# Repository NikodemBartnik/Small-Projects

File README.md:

# Small Projects
Here you can find some of my smaller projects. Most of them are Arduino based, there are also schematics and PCB design files. Feel free to fork and make it even better! Don't forget to share with others and with me, I would love to see how you adapt those small projects into something bigger :)

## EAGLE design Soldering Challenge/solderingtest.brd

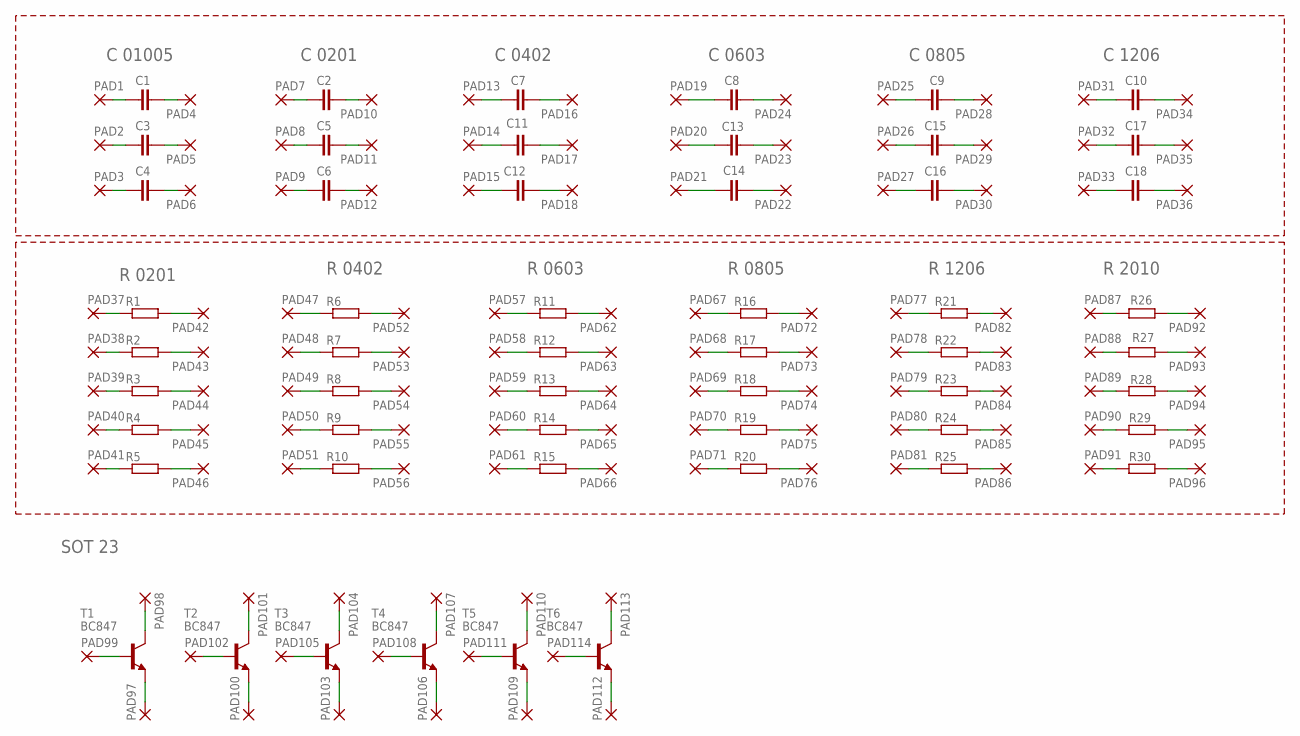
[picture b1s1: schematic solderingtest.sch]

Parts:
C1, C3, C4: C-EU01005; C01005
C2, C5, C6: C-EUC0201; C0201
C7, C11, C12: C-EUC0402; C0402
C8, C13, C14: C-EUC0603; C0603
C9, C15, C16: C-EUC0805; C0805
C10, C17, C18: C-EUC1206; C1206
PAD1, PAD2, PAD3, PAD4, PAD5, PAD6, PAD7, PAD8, PAD9, PAD10, PAD11, PAD12, PAD13, PAD14, PAD15, PAD16, PAD17, PAD18, PAD19, PAD20, PAD21, PAD22, PAD23, PAD24, PAD25, PAD26, PAD27, PAD28, PAD29, PAD30, PAD31, PAD32, PAD33, PAD34, PAD35, PAD36, PAD37, PAD38, PAD39, PAD40, PAD41, PAD42, PAD43, PAD44, PAD45, PAD46, PAD47, PAD48, PAD49, PAD50, PAD51, PAD52, PAD53, PAD54, PAD55, PAD56, PAD57, PAD58, PAD59, PAD60, PAD61, PAD62, PAD63, PAD64, PAD65, PAD66, PAD67, PAD68, PAD69, PAD70, PAD71, PAD72, PAD73, PAD74, PAD75, PAD76, PAD77, PAD78, PAD79, PAD80, PAD81, PAD82, PAD83, PAD84, PAD85, PAD86, PAD87, PAD88, PAD89, PAD90, PAD91, PAD92, PAD93, PAD94, PAD95, PAD96, PAD97, PAD98, PAD99, PAD100, PAD101, PAD102, PAD103, PAD104, PAD105, PAD106, PAD107, PAD108, PAD109, PAD110, PAD111, PAD112, PAD113, PAD114: 2,54/1,0
R1, R2, R3, R4, R5: R-EU_R0201; R0201
R6, R7, R8, R9, R10: R-EU_R0402; R0402
R11, R12, R13, R14, R15: R-EU_R0603; R0603
R16, R17, R18, R19, R20: R-EU_R0805; R0805
R21, R22, R23, R24, R25: R-EU_R1206; R1206
R26, R27, R28, R29, R30: R-EU_R2010; R2010
T1, T2, T3, T4, T5, T6: BC847; SOT23

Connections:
unnamed: C1.1, PAD1.1
unnamed: C3.1, PAD2.1
unnamed: C4.1, PAD3.1
unnamed: C4.2, PAD6.1
unnamed: C3.2, PAD5.1
unnamed: C1.2, PAD4.1
unnamed: C2.1, PAD7.1
unnamed: C2.2, PAD10.1
unnamed: C5.2, PAD11.1
unnamed: C5.1, PAD8.1
unnamed: C6.1, PAD9.1
unnamed: C6.2, PAD12.1
unnamed: C7.1, PAD13.1
unnamed: C7.2, PAD16.1
unnamed: C11.2, PAD17.1
unnamed: C11.1, PAD14.1
unnamed: C12.1, PAD15.1
unnamed: C12.2, PAD18.1
unnamed: C8.1, PAD19.1
unnamed: C8.2, PAD24.1
unnamed: C13.2, PAD23.1
unnamed: C14.2, PAD22.1
unnamed: C14.1, PAD21.1
unnamed: C13.1, PAD20.1
unnamed: C9.1, PAD25.1
unnamed: C15.1, PAD26.1
unnamed: C16.1, PAD27.1
unnamed: C9.2, PAD28.1
unnamed: C15.2, PAD29.1
unnamed: C16.2, PAD30.1
unnamed: C10.1, PAD31.1
unnamed: C17.1, PAD32.1
unnamed: C18.1, PAD33.1
unnamed: C10.2, PAD34.1
unnamed: C17.2, PAD35.1
unnamed: C18.2, PAD36.1
unnamed: PAD37.1, R1.1
unnamed: PAD42.1, R1.2
unnamed: PAD43.1, R2.2
unnamed: PAD44.1, R3.2
unnamed: PAD45.1, R4.2
unnamed: PAD40.1, R4.1
unnamed: PAD39.1, R3.1
unnamed: PAD38.1, R2.1
unnamed: PAD41.1, R5.1
unnamed: PAD46.1, R5.2
unnamed: PAD47.1, R6.1
unnamed: PAD52.1, R6.2
unnamed: PAD53.1, R7.2
unnamed: PAD54.1, R8.2
unnamed: PAD55.1, R9.2
unnamed: PAD56.1, R10.2
unnamed: PAD51.1, R10.1
unnamed: PAD50.1, R9.1
unnamed: PAD49.1, R8.1
unnamed: PAD48.1, R7.1
unnamed: PAD58.1, R12.1
unnamed: PAD59.1, R13.1
unnamed: PAD60.1, R14.1
unnamed: PAD61.1, R15.1
unnamed: PAD66.1, R15.2
unnamed: PAD65.1, R14.2
unnamed: PAD64.1, R13.2
unnamed: PAD63.1, R12.2
unnamed: PAD57.1, R11.1
unnamed: PAD62.1, R11.2
unnamed: PAD67.1, R16.1
unnamed: PAD68.1, R17.1
unnamed: PAD69.1, R18.1
unnamed: PAD70.1, R19.1
unnamed: PAD71.1, R20.1
unnamed: PAD76.1, R20.2
unnamed: PAD75.1, R19.2
unnamed: PAD74.1, R18.2
unnamed: PAD73.1, R17.2
unnamed: PAD72.1, R16.2
unnamed: PAD77.1, R21.1
unnamed: PAD78.1, R22.1
unnamed: PAD79.1, R23.1
unnamed: PAD80.1, R24.1
unnamed: PAD81.1, R25.1
unnamed: PAD82.1, R21.2
unnamed: PAD83.1, R22.2
unnamed: PAD84.1, R23.2
unnamed: PAD85.1, R24.2
unnamed: PAD86.1, R25.2
unnamed: PAD87.1, R26.1
unnamed: PAD88.1, R27.1
unnamed: PAD89.1, R28.1
unnamed: PAD90.1, R29.1
unnamed: PAD91.1, R30.1
unnamed: PAD92.1, R26.2
unnamed: PAD93.1, R27.2
unnamed: PAD94.1, R28.2
unnamed: PAD95.1, R29.2
unnamed: PAD96.1, R30.2
unnamed: PAD99.1, T1.1 (B)
unnamed: PAD98.1, T1.3 (C)
unnamed: PAD97.1, T1.2 (E)
unnamed: PAD102.1, T2.1 (B)
unnamed: PAD101.1, T2.3 (C)
unnamed: PAD100.1, T2.2 (E)
unnamed: PAD105.1, T3.1 (B)
unnamed: PAD104.1, T3.3 (C)
unnamed: PAD103.1, T3.2 (E)
unnamed: PAD108.1, T4.1 (B)
unnamed: PAD107.1, T4.3 (C)
unnamed: PAD106.1, T4.2 (E)
unnamed: PAD111.1, T5.1 (B)
unnamed: PAD110.1, T5.3 (C)
unnamed: PAD109.1, T5.2 (E)
unnamed: PAD114.1, T6.1 (B)
unnamed: PAD113.1, T6.3 (C)
unnamed: PAD112.1, T6.2 (E)

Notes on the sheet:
C 01005
C 0201
C 0402
C 0603
C 0805
C 1206
R 0201
R 0402
R 0603
R 0805
R 1206
R 2010
SOT 23

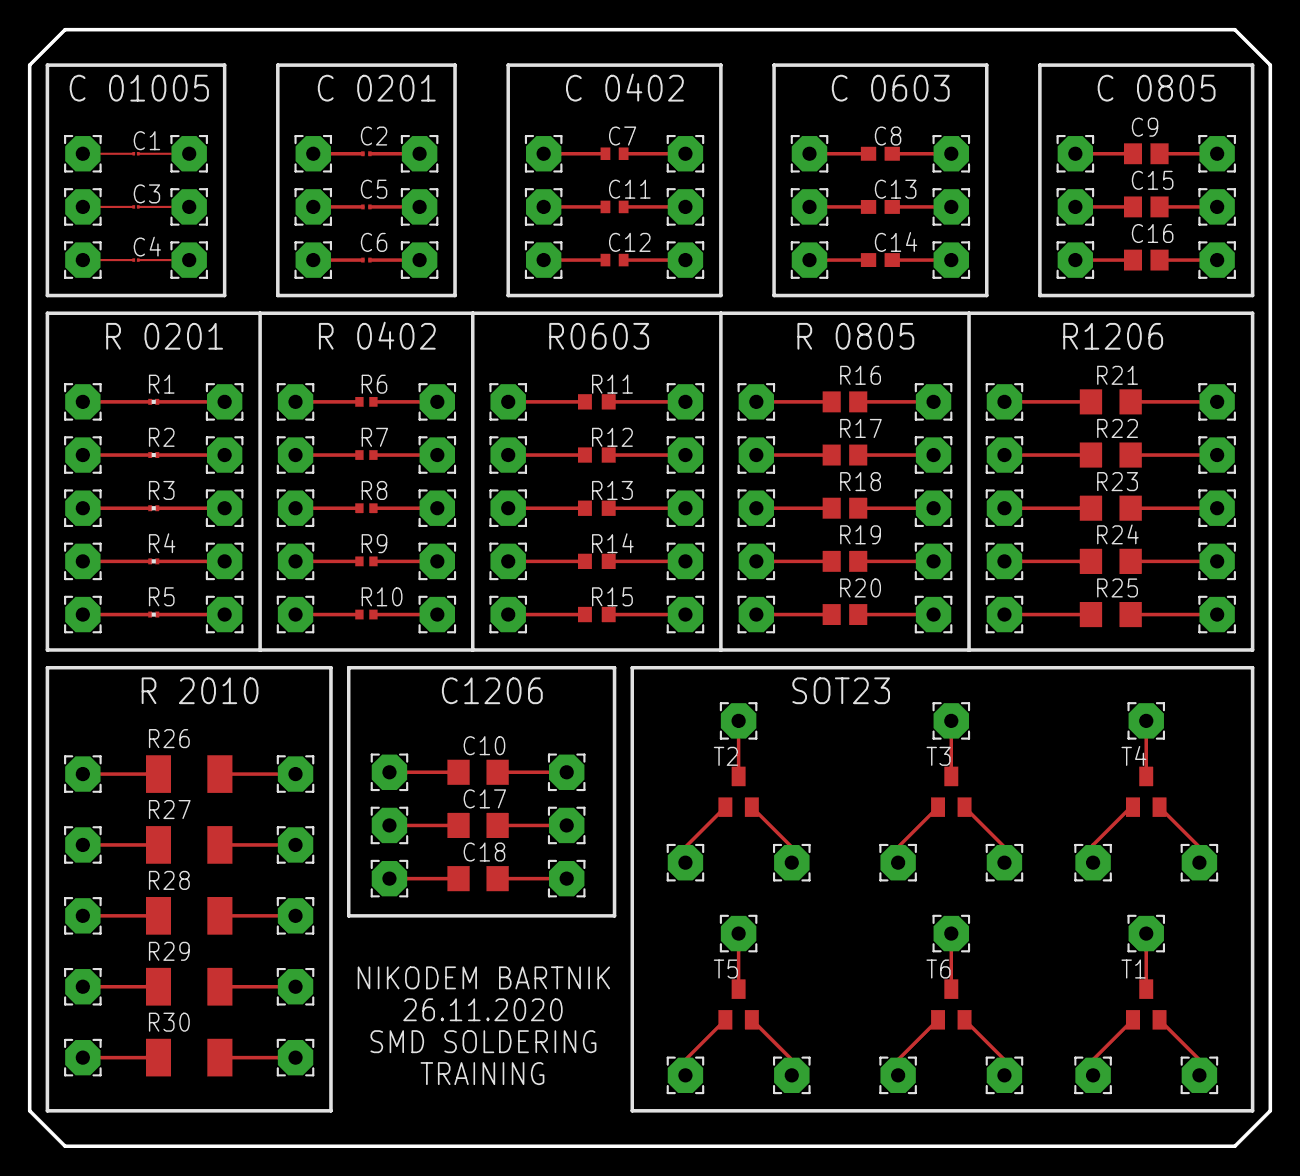
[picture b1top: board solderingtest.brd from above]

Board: 2 copper layers, 88.9 x 80.0 mm, 168 parts (0 on the bottom side), 114 nets.

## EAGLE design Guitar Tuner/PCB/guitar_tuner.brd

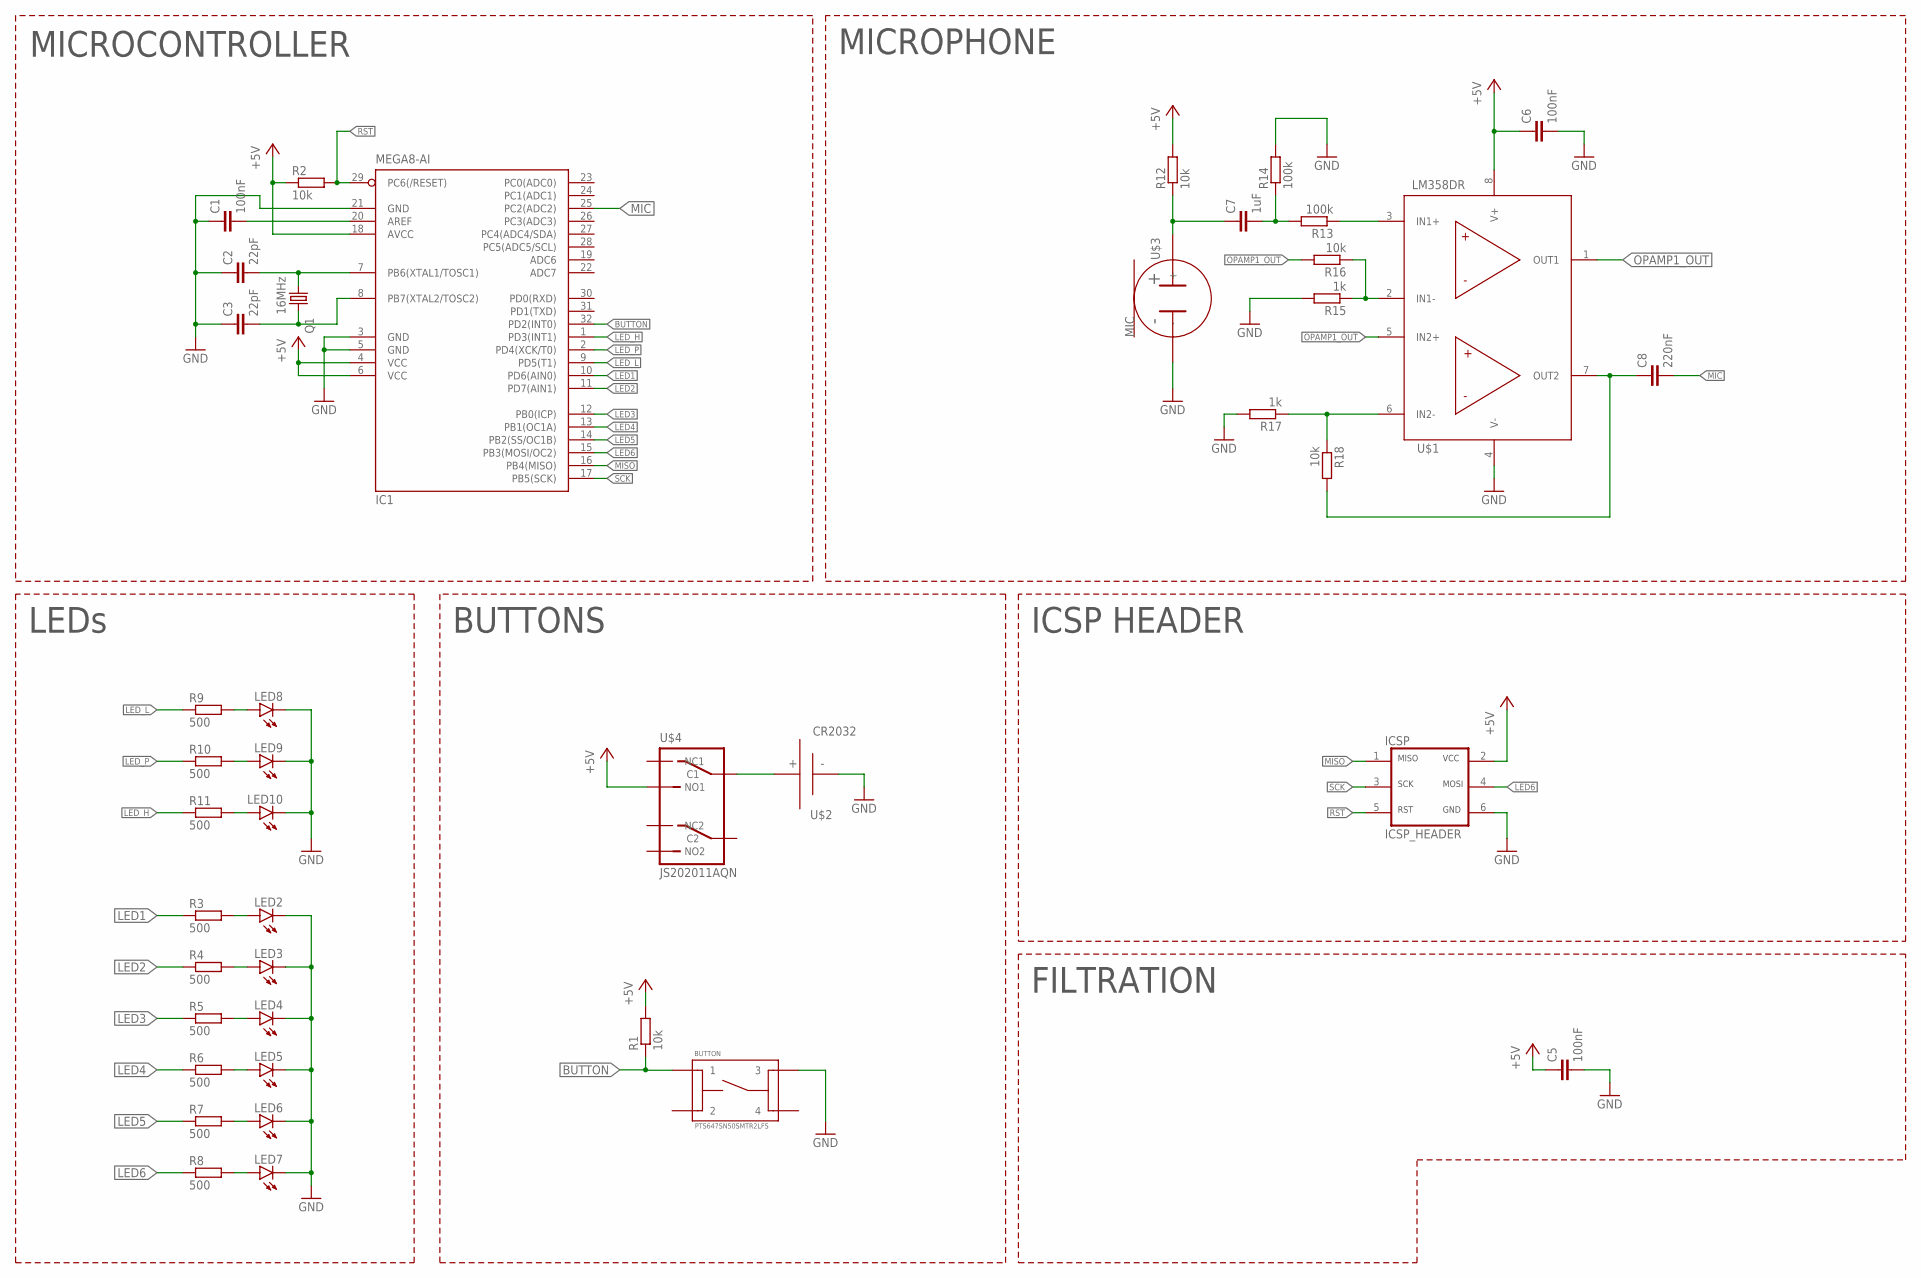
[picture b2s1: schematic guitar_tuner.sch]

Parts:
BUTTON: PTS647SN50SMTR2LFS; PTS647_SMD_TACTSWITCH
C1, C5, C6: 100nF; C0603
C2, C3: 22pF; C0603
C7: 1uF; C0603
C8: 220nF; C0603
IC1: MEGA8-AI; TQFP32-08
LED2, LED3, LED4, LED5, LED6, LED7, LED8, LED9, LED10: LEDCHIPLED_1206; CHIPLED_1206
Q1: 16MHz; 5.0X3.2_2
R1, R2, R12, R16, R18: 10k; R0603
R3, R4, R5, R6, R7, R8, R9, R10, R11: 500; R0603
R13, R14: 100k; R0603
R15, R17: 1k; R0603
U$1: LM358DRLM358DR_SOIC8; SOIC127P599X175-8N
U$2: BAT-HLD-001-THM
U$3: CMA-6542PF; 9.7MM_ELECTRET_MICROPHONE
U$4: JS202011AQN; JS202011AQN_DPDT
U$6: ICSP_HEADER

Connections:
+5V: C5.1, C6.1, IC1.4 (VCC), IC1.6 (VCC), IC1.18 (AVCC), R1.2, R2.1, R12.2, U$1.8 (V+), U$4.P$2 (NO1), U$6.2 (VCC)
BUTTON: BUTTON.P$1 (1), IC1.32 (PD2(INT0)), R1.1
GND: BUTTON.P$2 (3), C1.1, C2.1, C3.1, C5.2, C6.2, IC1.3 (GND), IC1.5 (GND), IC1.21 (GND), LED2.C, LED3.C, LED4.C, LED5.C, LED6.C, LED7.C, LED8.C, LED9.C, LED10.C, R14.2, R15.2, R17.2, U$1.4 (V-), U$2.P$6 (GND), U$3.P$2 (-), U$6.6 (GND)
LED1: IC1.10 (PD6(AIN0)), R3.1
LED2: IC1.11 (PD7(AIN1)), R4.1
LED3: IC1.12 (PB0(ICP)), R5.1
LED4: IC1.13 (PB1(OC1A)), R6.1
LED5: IC1.14 (PB2(SS/OC1B)), R7.1
LED6: IC1.15 (PB3(MOSI/OC2)), R8.1, U$6.4 (MOSI)
LED_H: IC1.1 (PD3(INT1)), R11.1
LED_L: IC1.9 (PD5(T1)), R9.1
LED_P: IC1.2 (PD4(XCK/T0)), R10.1
MIC: C8.2, IC1.25 (PC2(ADC2))
MISO: IC1.16 (PB4(MISO)), U$6.1 (MISO)
unnamed: C2.2, IC1.7 (PB6(XTAL1/TOSC1)), Q1.1
unnamed: C3.2, IC1.8 (PB7(XTAL2/TOSC2)), Q1.2
unnamed: C1.2, IC1.20 (AREF)
unnamed: U$2.P$1 (5V), U$2.P$2 (5V), U$2.P$3 (5V), U$2.P$4 (5V), U$2.P$5 (5V), U$4.P$3 (C1)
unnamed: C7.1, R12.1, U$3.P$1 (+)
unnamed: LED2.A, R3.2
unnamed: LED3.A, R4.2
unnamed: LED4.A, R5.2
unnamed: LED5.A, R6.2
unnamed: LED6.A, R7.2
unnamed: LED7.A, R8.2
unnamed: LED9.A, R10.2
unnamed: LED8.A, R9.2
unnamed: LED10.A, R11.2
unnamed: C7.2, R13.2, R14.1
unnamed: R13.1, U$1.3 (IN1+)
unnamed: R15.1, R16.1, U$1.2 (IN1-)
unnamed: R17.1, R18.1, U$1.6 (IN2-)
unnamed: C8.1, R18.2, U$1.7 (OUT2)
OPAMP1_OUT: R16.2, U$1.1 (OUT1), U$1.5 (IN2+)
RST: IC1.29 (PC6(/RESET)), R2.2, U$6.5 (RST)
SCK: IC1.17 (PB5(SCK)), U$6.3 (SCK)

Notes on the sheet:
MICROCONTROLLER
MICROPHONE
LEDs
BUTTONS
ICSP HEADER
FILTRATION

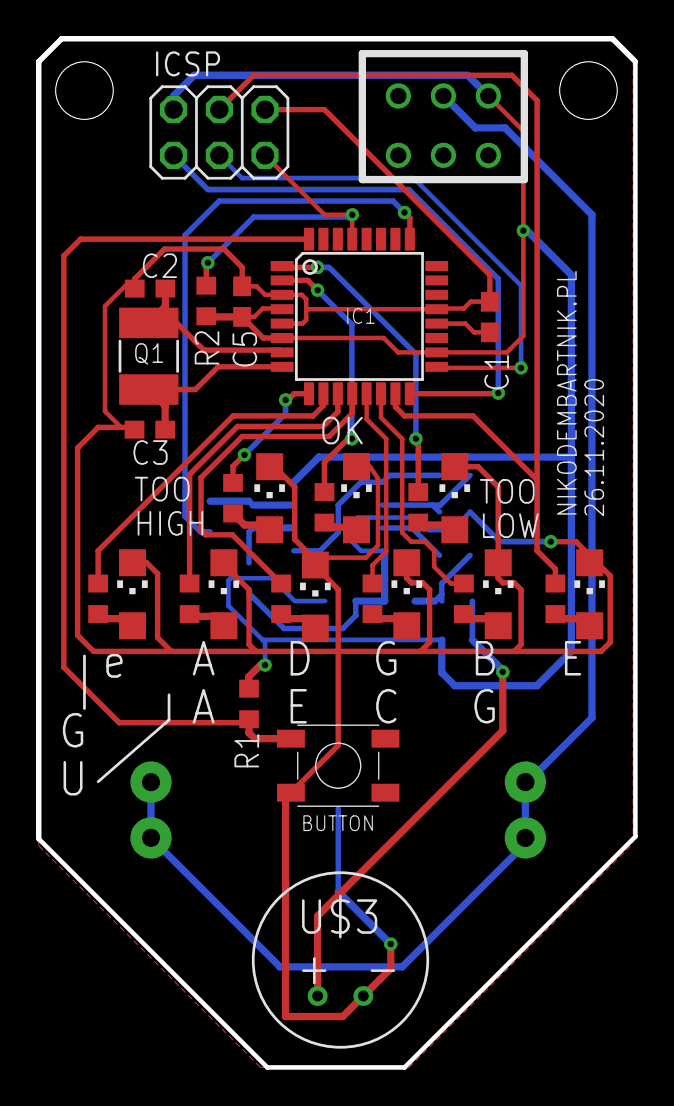
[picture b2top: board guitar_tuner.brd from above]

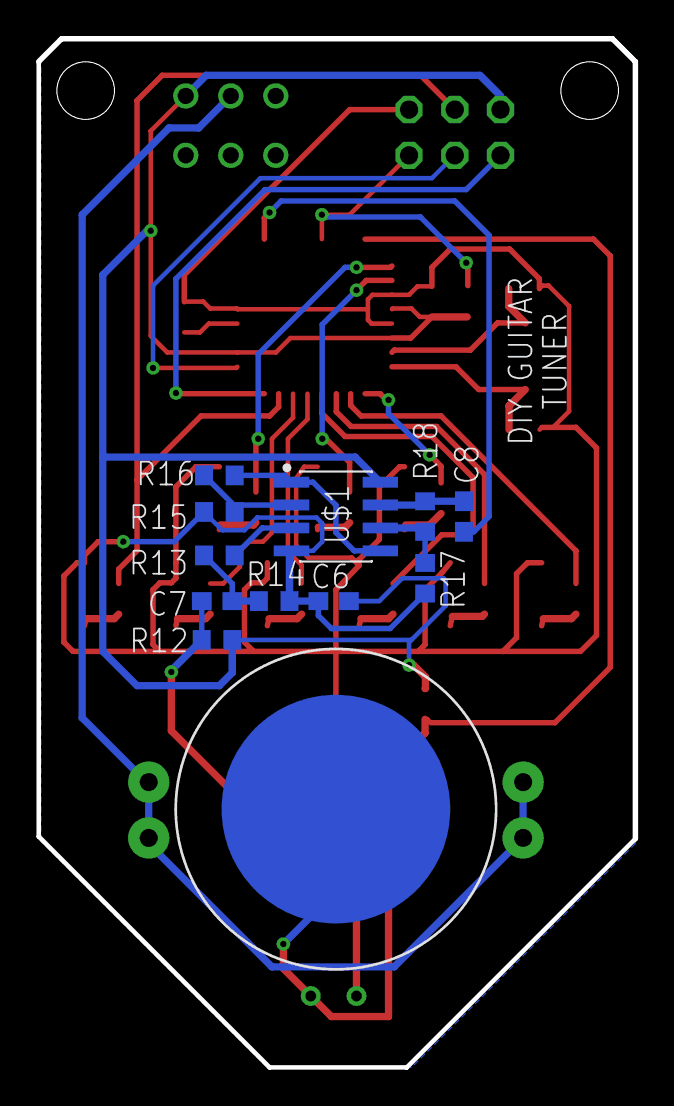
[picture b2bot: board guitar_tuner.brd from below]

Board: 2 copper layers, 33.1 x 57.1 mm, 42 parts (12 on the bottom side), 36 nets.

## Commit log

2021-01-14 Moved Encoded Motor driver from separete repo
2021-01-14 Moved sprint race timer repo
2021-01-14 Moved christmass tree PCB repo
2021-01-14 Moved RC Robot repo
2021-01-14 Moved Watering System repo
2021-03-03 Added Soldering Challenge files

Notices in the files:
parts and their libraries:
crystal-geyer_V1_0: Copyright: Geyer-Electronic
